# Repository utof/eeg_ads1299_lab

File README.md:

# ADS1299 Learning Lab

**Start without buying anything.** This is a runnable Python learning environment for EEG-like signals, an illustrative electrode/input circuit, signed 24-bit conversion, data transport, signal quality, and a small machine-learning experiment.

It is **not a finished EEG recorder, a validated PCB, or permission to attach a circuit to a person**. The firmware is a board-dependent **bench-only starter** using the ADS1299's internal test/short circuits. **Rev A selects an ADS1299-4 daughterboard plus ESP32-S3-DevKitC-1-N8R8 for simulation/schematic work; none of the hardware-review or body-connection gates are approved.**

## Open these first

| File | What it does for you |
|---|---|
| [START_HERE.html](START_HERE.html) | Offline visual walkthrough, provisional digital pin map, interactive gain/offset calculator. Open with the rest of the repository available. |
| [Agent instructions](AGENTS.md) / [GitHub publication runbook](docs/REPOSITORY_PUBLICATION.md) | Fresh assistant starts here; working publication methods, review boundaries and recovery checks. |
| [Development guide](docs/DEVELOPMENT.md) | Locked installation, one quality command, test-first changes, strict typing, and enforced public interfaces. |
| [DX validation record](docs/DX_VALIDATION.md) | A dated CI run with software tests, actual ngspice execution, native helper tests, and limitations. |
| [Historical results report](docs/RESULTS.md) | Original measured outputs and evidence; retained rather than overwritten by routine CI. |
| [Learning guide](docs/LEARNING_GUIDE.md) | A beginner explanation of the electronics, simulations, signal processing, and small exercises. |
| [Hardware guide](docs/HARDWARE_GUIDE.md) | Purchasing gate, $100 budget constraint, conditional wiring, bench tests, and the body-connection boundary. |
| [Rev A hardware baseline](docs/HARDWARE_BASELINE_REV_A.md) | Selected ADS1299-4 + ESP32-S3 components, machine-readable BOM/profile, fail-closed gates, and ordered next work. |
| [Experiments guide](docs/EXPERIMENTS.md) | From synthetic alpha to a future controlled meditation experiment, without confusing artifacts with consciousness. |
| [Next-session handoff](docs/LLM_HANDOFF.md) | Give this to a future assistant together with the source and validation records. |

The earlier uploaded reports are background, not software dependencies. This package does not depend on their old ZIP links or on an AD8232/ADS1115.

**For assistant-run repository work:** follow the [hosted capability preflight](docs/REPOSITORY_PUBLICATION.md#hosted-capability-preflight)
before proposing downloads or local setup. The installation commands below are
for people choosing to run the lab locally, not prerequisites for hosted editing
or KiCad validation through the connected tools.

## First run: Linux, macOS, or Windows

Use Python **3.11 or newer**; Python 3.13 is the development default. CI exercises clean locked installations on Linux with Python 3.11 and 3.13. macOS and Windows are not currently covered by that CI matrix. `pyproject.toml` and `uv.lock` define the current dependencies; `requirements-tested.txt` is a historical validation record.

Clone or extract the repository, then open a terminal **inside `eeg_ads1299_lab`**:

```bash
uv sync --locked --all-extras
uv run --locked python run_lab.py demo
uv run --locked python -m tools.check
```

Install **uv 0.12.18** first using the [official installation instructions](https://docs.astral.sh/uv/getting-started/installation/). The standalone installer supports an explicit version in its URL. All project commands use `uv`; do not use a separately activated environment or bare Python/pip to run or modify this project. The editable installation makes imports work outside the checkout too.

The demo makes `reports/demo/synthetic_recording.npz`, event/quality CSVs, an analysis JSON, and four PNG figures. Live commands default to ignored `reports/`; committed `results/` examples are historical evidence. Use `--out reports/my_demo` for a separate run. The seed is fixed, but numerical outputs can vary slightly across dependency versions.

The quality command checks formatting, Ruff lint, strict Pyrefly typing, cognitive complexity, Tach import boundaries, the hardware baseline, software tests, and measured branch coverage. It includes the hardware-baseline tests that formerly needed a separate discovery command. Logs and reports go under `reports/check/`, not over historical evidence.

**A successful software check is not a native-simulator, firmware-target, or hardware pass.** Run the explicit native command below for native integration. `uv run --locked python run_lab.py verify` is now a compatibility entry point to the **same** `tools.check` gate. Add `--native` for native integration; `--require-ngspice` remains an alias. There is no competing historical-report verifier.

Before making changes, read [AGENTS.md](AGENTS.md) and install both the pre-commit and commit-message hooks:

```bash
uv run --locked pre-commit install
```

## Run a circuit simulation

```bash
uv run --locked python run_lab.py circuits --out reports/circuits
```

This solves the existing illustrative passive circuit using Python's linear algebra, writes response/tolerance CSVs, and exports two `.cir` files. The numerical solver is **not ngspice**. There is no transistor-level ADS1299 model, and the next Rev A-specific input-network model is separate work.

For a real ngspice cross-check and the full native gate on Debian/Ubuntu/Linux Mint:

```bash
sudo apt update
sudo apt install --no-install-recommends ngspice g++ nodejs
uv run --locked python run_lab.py circuits --require-ngspice --out reports/circuits
uv run --locked python -m tools.check --native
```

The strict commands fail when required tools are absent. The DX CI run recorded in [DX_VALIDATION.md](docs/DX_VALIDATION.md) actually executed ngspice and compared both educational circuits with the independent numerical solution. That newer CI evidence does not change what ran in the original historical validation environment. Simulator logs remain under the output folder.

## Three useful changes

```bash
# Negative control: remove the planted condition difference.
uv run --locked python run_lab.py demo --null-effect --out reports/my_null

# Eight physical channels and 60-Hz residual line interference.
uv run --locked python run_lab.py demo --channels 8 --line-hz 60 --out reports/eight_channels

# Edit a copy of this JSON to change gain, offset, or artifact size.
uv run --locked python run_lab.py demo --config configs/demo.json --out reports/custom
```

Changing a JSON changes the **simulation**, not a physical board. The firmware does not read `configs/demo.json` or the board-review worksheet.

## Test the recording path with no electronics

```bash
uv run --locked python -m tools.check --native
```

The native gate includes the real localhost UDP loopback: nine seconds of synthetic packets with samples 1000 and 2000 deliberately omitted, CSV decoding, and a gap-safe quality report. It checks 2,248 accepted packets and two missing samples. Unexpected extra loss causes a failure rather than a reassuring-looking plot. To run only the loopback, use `uv run --locked python -m tools.run_loopback --out reports/loopback`.

For manual control, use two terminals:

```bash
# Terminal A
uv run --locked python run_lab.py receive --seconds 15 --out reports/practice.bin
```

```bash
# Terminal B, while A is listening
uv run --locked python run_lab.py replay --seconds 8 --drop-every 1000
```

Then:

```bash
uv run --locked python run_lab.py decode reports/practice.bin --out reports/practice.csv
uv run --locked python run_lab.py inspect reports/practice.csv --out reports/practice_quality
```

Keep the `.json` metadata beside the decoded CSV. New captures include a SHA-256 binding the pair; inspection rejects a mismatched generation. Legacy captures without a digest remain readable with an explicit caution. The inspector analyzes only uninterrupted four-second windows. It reports DC offset separately and never fills gaps to manufacture a continuous spectrum. The receiver defaults to localhost; actual LAN use requires `--host 0.0.0.0`, private-network firewall permission, and the computer's LAN address in the firmware. UDP is unencrypted; never expose the port to the public internet.

## What is in the source?

```text
lab/adc.py              Ideal code scaling, range/headroom checks, sinc³ model
lab/analog/            Public analog facade; internal solver, SPICE, and report modules
lab/data_types.py      Typed numerical arrays and data/report contracts
lab/validation.py      Runtime validation at external-data boundaries
lab/signals.py          Deterministic, explicitly synthetic recordings
lab/dsp.py              Quality screens, band power, session-held-out classifier
lab/protocol.py         ADS frame decoding, custom packets, CRC and counters
lab/acquisition.py      UDP/optional bench serial logging and CSV decoding
lab/inspect_capture.py  Gap-safe bench spectra and quality reports
lab/recording.py        Synthetic recording validation and atomic NPZ persistence
lab/pipeline.py         Demo outputs and figures; compatibility persistence re-exports
hardware/rev_a/         Hardware-contract facade, checker, data, and tests
firmware/              Original-ESP32 bench starter; NOT target-compiled by the DX gate
configs/               Editable demo settings and hardware-review worksheet
results/               Historical example recordings, figures, logs, and reports
reports/               Ignored outputs from current quality/simulation runs
tests/                 Regression, property, architecture, and workflow tests
tools/check.py         Shared local/CI quality command
tools/commit_messages.py Conventional Commit hook and actual-history validation
tach.toml              Enforced public interfaces and dependency direction
```

The firmware's default `BOARD_PROFILE_REVIEWED = false` intentionally prevents acquisition startup. Changing that setting acknowledges **bench digital wiring only**, not body-use approval. Do not bypass it just to see a waveform.

## Rev A input-network study

The selected Rev A input components now feed a reproducible passive-network study, rather than remaining isolated hardware JSON. Start with the numerical calculation; then run the independent simulator comparison when ngspice is installed:

```bash
uv run --locked python -m lab.rev_a --out reports/rev_a_input
uv run --locked python -m lab.rev_a --require-ngspice --out reports/rev_a_input_native
```

The study validates and loads the locked 4.99 kOhm / 4.7 nF component values and BOM tolerances, checks an ideal-source reference, compares balanced and mismatched source impedances, evaluates eight tolerance corners per case, and reports 50/60 Hz common-mode conversion plus hypothetical DC leakage sensitivity. The native command actually runs six ngspice comparisons. `uv run --locked python -m tools.check --native` includes this study and retains its evidence under `reports/check/rev_a_input/`.

All source/load/parasitic assumptions appear in the report. Clamps remain DNP. **This is not an ADS1299 silicon, distributed-cable, BIAS-loop, physical-hardware or human-use safety model.** Read the [Rev A study guide](docs/REV_A_INPUT_STUDY.md) before interpreting the numbers.

## Contributing: uv and Conventional Commits

Use `uv sync --locked --all-extras` and `uv run --locked ...` for project work. Child processes launched with `sys.executable` inherit that locked interpreter; they do not create a second environment. CI bootstraps uv itself separately, then uses the same locked commands.

Commit subjects follow [Conventional Commits 1.0.0](https://www.conventionalcommits.org/en/v1.0.0/):

```text
feat(simulation): add a Rev A input-network sweep
fix(recording): reject discontinuous sample times
refactor(acquisition): stream decoded packets
chore(dx): synchronize issue labels
```

Use lowercase `feat`, `fix`, `docs`, `style`, `refactor`, `perf`, `test`, `build`, `ci`, `chore`, or `revert`; an optional lowercase scope describes the affected component. A breaking change uses `!` after the type/scope and should explain the incompatibility in a `BREAKING CHANGE:` footer. Subjects must have a nonempty description and no trailing whitespace.

The installed `commit-msg` hook checks the subject. CI checks **actual commits introduced by the PR**, not just its title. Old history is grandfathered. Actual merge commits are exempt, but writing “Merge” on a single-parent commit is not a bypass. **Merge PRs with merge commits: no squash and no history rewriting.** Validate a range locally with:

```bash
uv run --locked python -m tools.commit_messages --base origin/main --head HEAD
uv run --locked python -m tools.check --native
```

Issues use one `type/*`, one `priority/*`, and applicable `area/*` labels. Examples: `type/bug` + `priority/high` + `area/acquisition`, or `type/refactor` + `priority/medium` + `area/dx`. [The label manifest](.github/labels.json) owns names, colors, and descriptions; trusted-main housekeeping synchronizes it without deleting unrelated labels. Merged same-repository PR branches are removed only after ancestry and exact-head checks. Active or changed branches are retained.

Read [the adversarial review](docs/ADVERSARIAL_REVIEW.md) for the architecture verdict, reproduced failures, corrections, and remaining limits.

## Troubleshooting

| Symptom | First action |
|---|---|
| `ModuleNotFoundError` | Run `uv sync --locked --all-extras` and use `uv run --locked` with the repository environment. |
| Missing ngspice or native compiler | Install the required tool; do not count numerical Python tests as native execution. |
| Quality gate failed | Read the named log and `reports/check/CHECK_REPORT.json`; do not bypass the check. |
| `All epochs rejected` | Inspect gain, differential DC offset, and quality flags. An overrange input is an expected negative test. |
| No UDP packets | First repeat localhost loopback. Then inspect the private LAN address, firewall, and UDP port. |
| No four-second spectral windows | The capture is too short or fragmented. Fix acquisition before interpreting spectra. |
| Unexpected ESP32 or board pins | Stop; the supplied firmware pin map is not generic to every ESP32/ADS1299 module. |
| Matplotlib cache permission warning | Set `MPLCONFIGDIR` to a writable directory; no special font installation is required. |

Read [SOURCES.md](docs/SOURCES.md) for primary references and [MODEL_SCOPE.md](docs/MODEL_SCOPE.md) for model boundaries.

### Bounded BIAS overload hypothesis

`uv run --locked python -m lab.rev_a_bias_overload --require-ngspice` compares
a stated one-pole rail/slew hypothesis with ngspice while preserving feedback
capacitor charge. It is not measured ADS1299 overload recovery. Read
[the scope, source limits and numerical checks](docs/REV_A_BIAS_OVERLOAD.md).

### Shared-source analog-feed hypothesis

Run `uv run --locked python -m lab.rev_a_supply` for five independently checked
startup/burst cases of the selected analog-feed path. See
[the study and its assumptions](docs/REV_A_SUPPLY_STUDY.md). A completed numerical
comparison may expose a modeled rail-margin breach; neither outcome qualifies
the board or the separate TPS7A20 model.

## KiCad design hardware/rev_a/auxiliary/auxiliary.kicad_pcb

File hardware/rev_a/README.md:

# Rev A component baseline

Read [the hardware decision](../../docs/HARDWARE_BASELINE_REV_A.md) first.

**Selected:** ADS1299-4PAGR, ESP32-S3-DevKitC-1-N8R8, internal ADC reference/clock,
5 V unipolar bench power, and ADC-only TPS7A2033PDBVR regulation.

**Not authorized:** fabrication, purchasing, external-input operation or body connection.
The review flags are deliberately false. These JSON files are a design contract,
not a firmware implementation or a validated KiCad schematic.

```bash
python hardware/rev_a/check_baseline.py
python -m unittest discover -s hardware/rev_a -p 'test_*.py' -v
```

Run those commands from the repository root. Python 3.10+ and no third-party
packages are required. The checker also works when invoked by absolute path.

- `board_profile.json`: selected operating point, proposed GPIO/header assignments and review gates.
- `bom.json`: exact selected MPNs, reference counts, FIT/DNP population and planning costs.
- `sources.json`: primary sources, original-report SHA-256 hashes and access limitations.

This baseline was integrated after inspecting live `main` at
`31205de841c577c373532fbc9d065fa81d0a6ac8`. The existing firmware remains
unchanged and its board/target review guard stays fail-closed. The repository's
entry-point docs link here so future work does not reopen the component decision
by accident. Run the existing project tests and ngspice baseline on this branch
before changing the analog model or porting firmware to the S3.

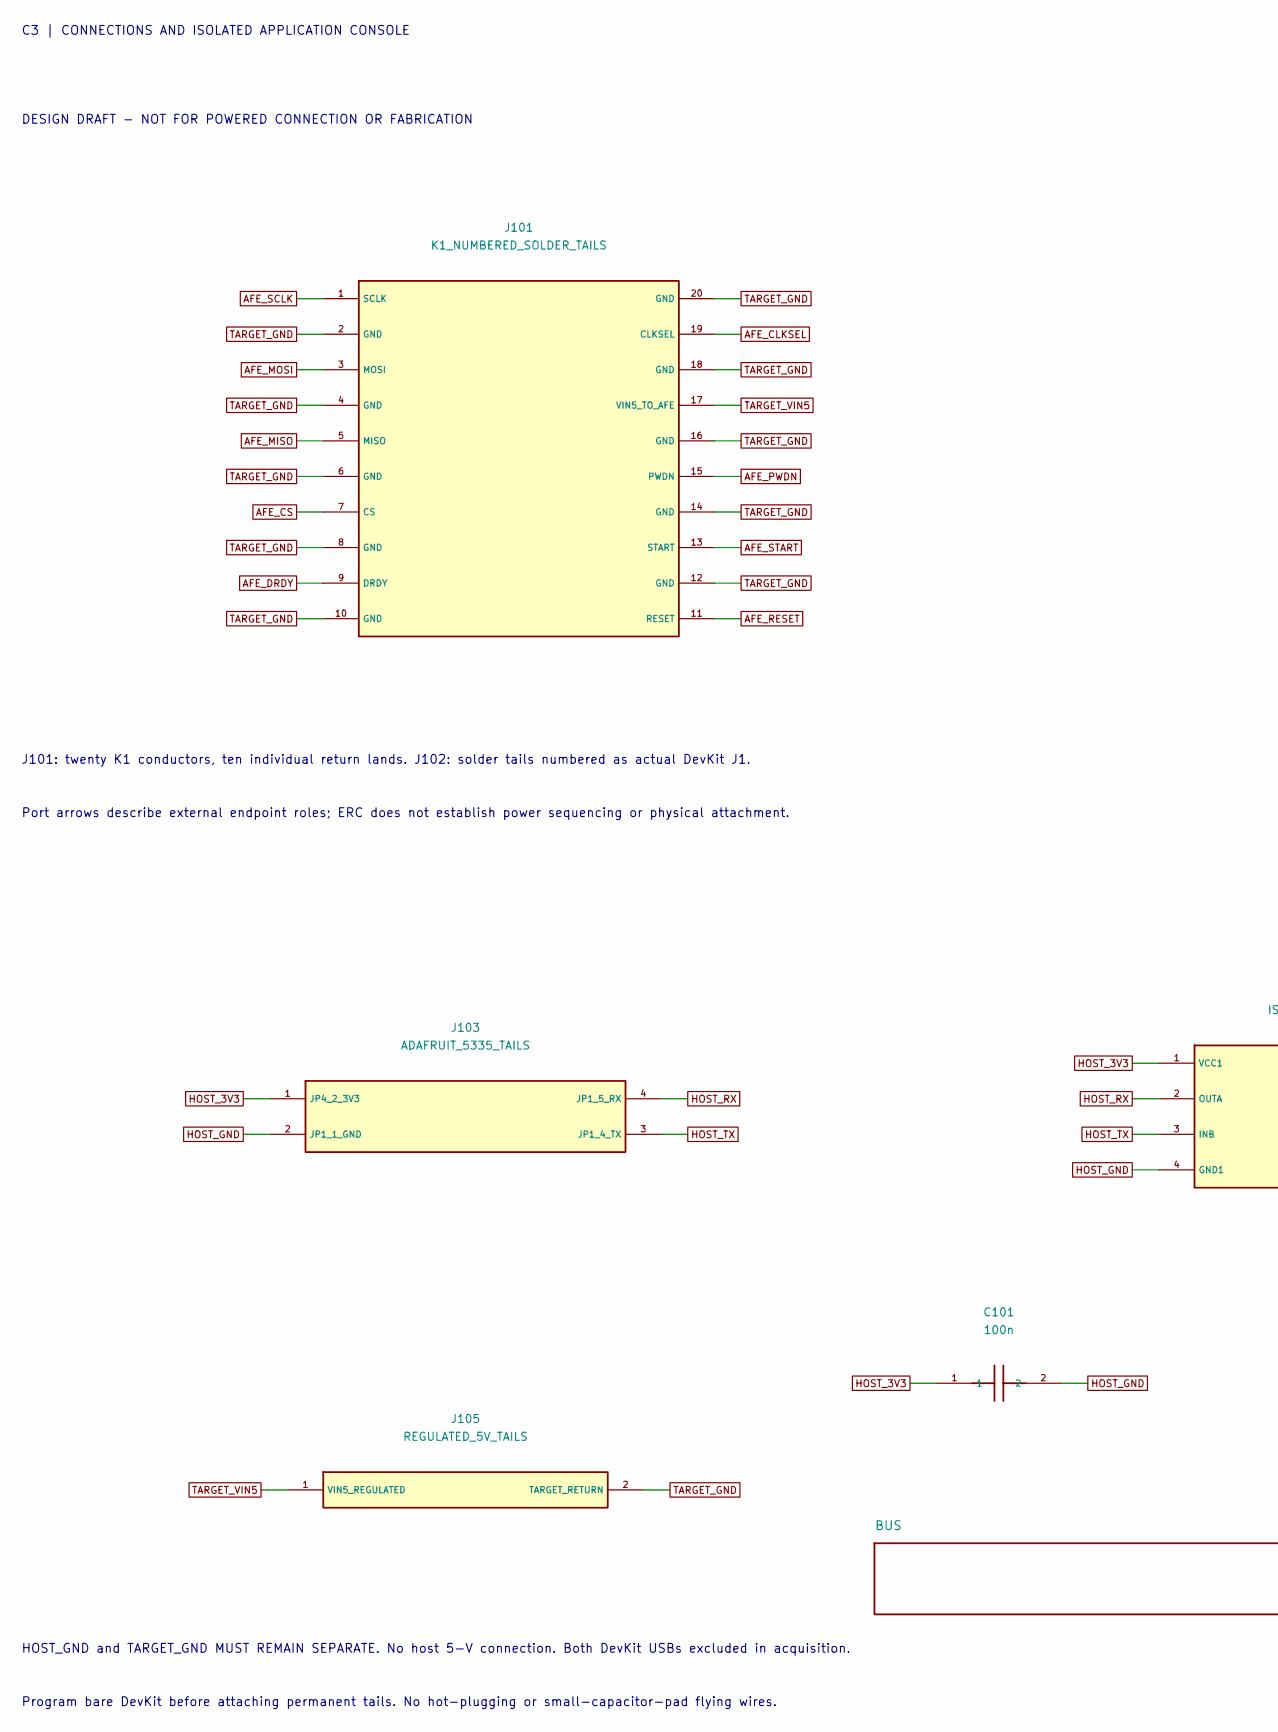
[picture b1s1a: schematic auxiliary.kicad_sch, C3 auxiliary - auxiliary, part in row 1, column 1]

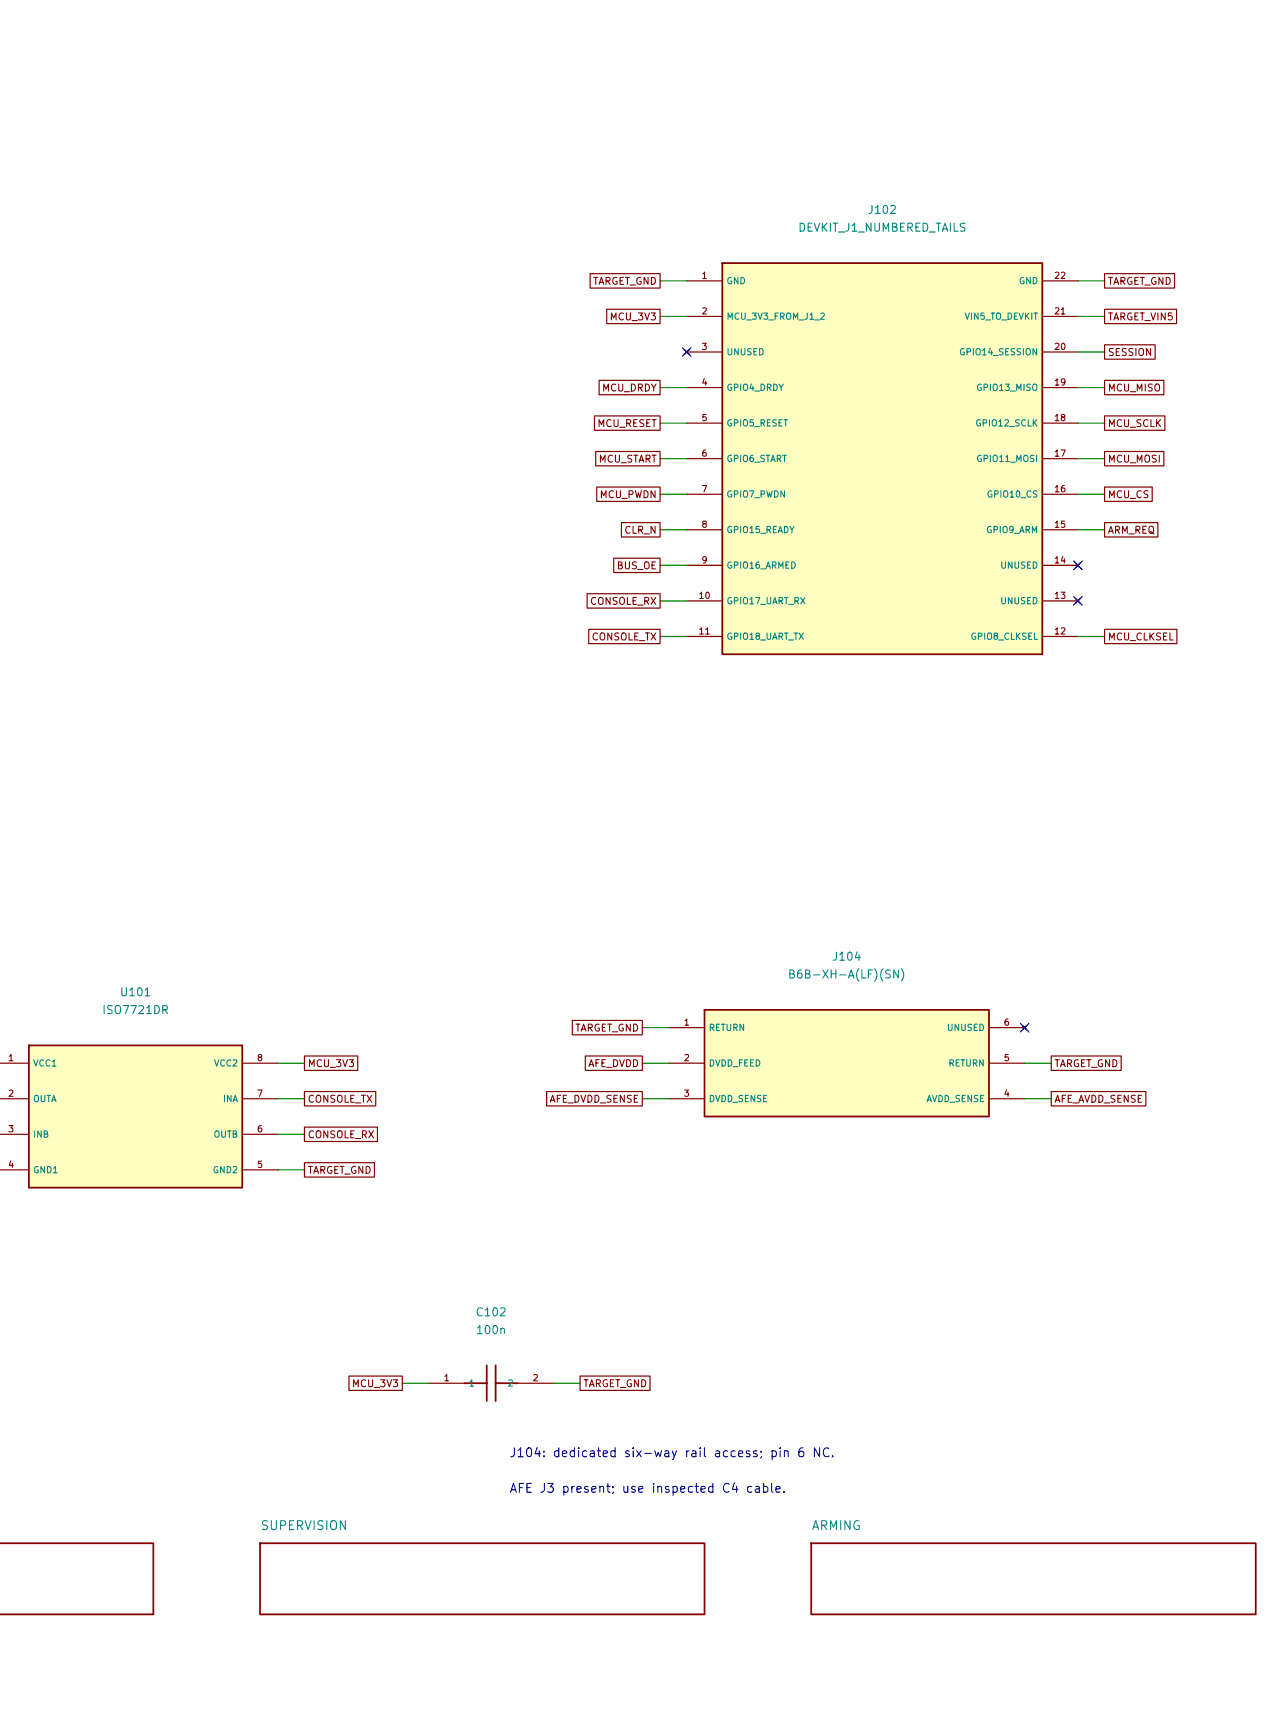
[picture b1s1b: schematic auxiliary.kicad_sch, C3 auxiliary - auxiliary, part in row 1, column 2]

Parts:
C101, C102: 100n; C_0603_1608Metric; MPN C0603C104K5RACTU
J101: K1_NUMBERED_SOLDER_TAILS; SolderTails_20; MPN PCB_LANDINGS_ONLY
J102: DEVKIT_J1_NUMBERED_TAILS; SolderTails_22; MPN PCB_LANDINGS_ONLY
J103: ADAFRUIT_5335_TAILS; SolderTails_4; MPN PCB_LANDINGS_ONLY
J104: B6B-XH-A(LF)(SN); JST_XH_B6B-XH-A_1x06_P2.50mm_Vertical; MPN B6B-XH-A(LF)(SN)
J105: REGULATED_5V_TAILS; SolderTails_2; MPN PCB_LANDINGS_ONLY
U101: ISO7721DR; SOIC-8_3.9x4.9mm_P1.27mm; MPN ISO7721DR

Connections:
AFE_AVDD_SENSE: J104.4 (AVDD_SENSE); also elsewhere on the board
AFE_CLKSEL: J101.19 (CLKSEL); also elsewhere on the board
AFE_CS: J101.7 (CS); also elsewhere on the board
AFE_DRDY: J101.9 (DRDY); also elsewhere on the board
AFE_DVDD: J104.2 (DVDD_FEED); also elsewhere on the board
AFE_DVDD_SENSE: J104.3 (DVDD_SENSE); also elsewhere on the board
AFE_MISO: J101.5 (MISO); also elsewhere on the board
AFE_MOSI: J101.3 (MOSI); also elsewhere on the board
AFE_PWDN: J101.15 (PWDN); also elsewhere on the board
AFE_RESET: J101.11 (RESET); also elsewhere on the board
AFE_SCLK: J101.1 (SCLK); also elsewhere on the board
AFE_START: J101.13 (START); also elsewhere on the board
ARM_REQ: J102.15 (GPIO9_ARM); also elsewhere on the board
BUS_OE: J102.9 (GPIO16_ARMED); also elsewhere on the board
CLR_N: J102.8 (GPIO15_READY); also elsewhere on the board
CONSOLE_RX: J102.10 (GPIO17_UART_RX), U101.6 (OUTB)
CONSOLE_TX: J102.11 (GPIO18_UART_TX), U101.7 (INA)
HOST_3V3: C101.1, J103.1 (JP4_2_3V3), U101.1 (VCC1)
HOST_GND: C101.2, J103.2 (JP1_1_GND), U101.4 (GND1)
HOST_RX: J103.4 (JP1_5_RX), U101.2 (OUTA)
HOST_TX: J103.3 (JP1_4_TX), U101.3 (INB)
MCU_3V3: C102.1, J102.2 (MCU_3V3_FROM_J1_2), U101.8 (VCC2); also elsewhere on the board
MCU_CLKSEL: J102.12 (GPIO8_CLKSEL); also elsewhere on the board
MCU_CS: J102.16 (GPIO10_CS); also elsewhere on the board
MCU_DRDY: J102.4 (GPIO4_DRDY); also elsewhere on the board
MCU_MISO: J102.19 (GPIO13_MISO); also elsewhere on the board
MCU_MOSI: J102.17 (GPIO11_MOSI); also elsewhere on the board
MCU_PWDN: J102.7 (GPIO7_PWDN); also elsewhere on the board
MCU_RESET: J102.5 (GPIO5_RESET); also elsewhere on the board
MCU_SCLK: J102.18 (GPIO12_SCLK); also elsewhere on the board
MCU_START: J102.6 (GPIO6_START); also elsewhere on the board
SESSION: J102.20 (GPIO14_SESSION); also elsewhere on the board
TARGET_GND: C102.2, J101.2 (GND), J101.4 (GND), J101.6 (GND), J101.8 (GND), J101.10 (GND), J101.12 (GND), J101.14 (GND), J101.16 (GND), J101.18 (GND), J101.20 (GND), J102.1 (GND), J102.22 (GND), J104.1 (RETURN), J104.5 (RETURN), J105.2 (TARGET_RETURN), U101.5 (GND2); also elsewhere on the board
TARGET_VIN5: J101.17 (VIN5_TO_AFE), J102.21 (VIN5_TO_DEVKIT), J105.1 (VIN5_REGULATED); also elsewhere on the board

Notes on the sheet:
C3 | CONNECTIONS AND ISOLATED APPLICATION CONSOLE
DESIGN DRAFT - NOT FOR POWERED CONNECTION OR FABRICATION
J101: twenty K1 conductors, ten individual return lands. J102: solder tails numbered as actual DevKit J1.
Port arrows describe external endpoint roles; ERC does not establish power sequencing or physical attachment.
J104: dedicated six-way rail access; pin 6 NC.
AFE J3 present; use inspected C4 cable.
HOST_GND and TARGET_GND MUST REMAIN SEPARATE. No host 5-V connection. Both DevKit USBs excluded in acquisition.
Program bare DevKit before attaching permanent tails. No hot-plugging or small-capacitor-pad flying wires.

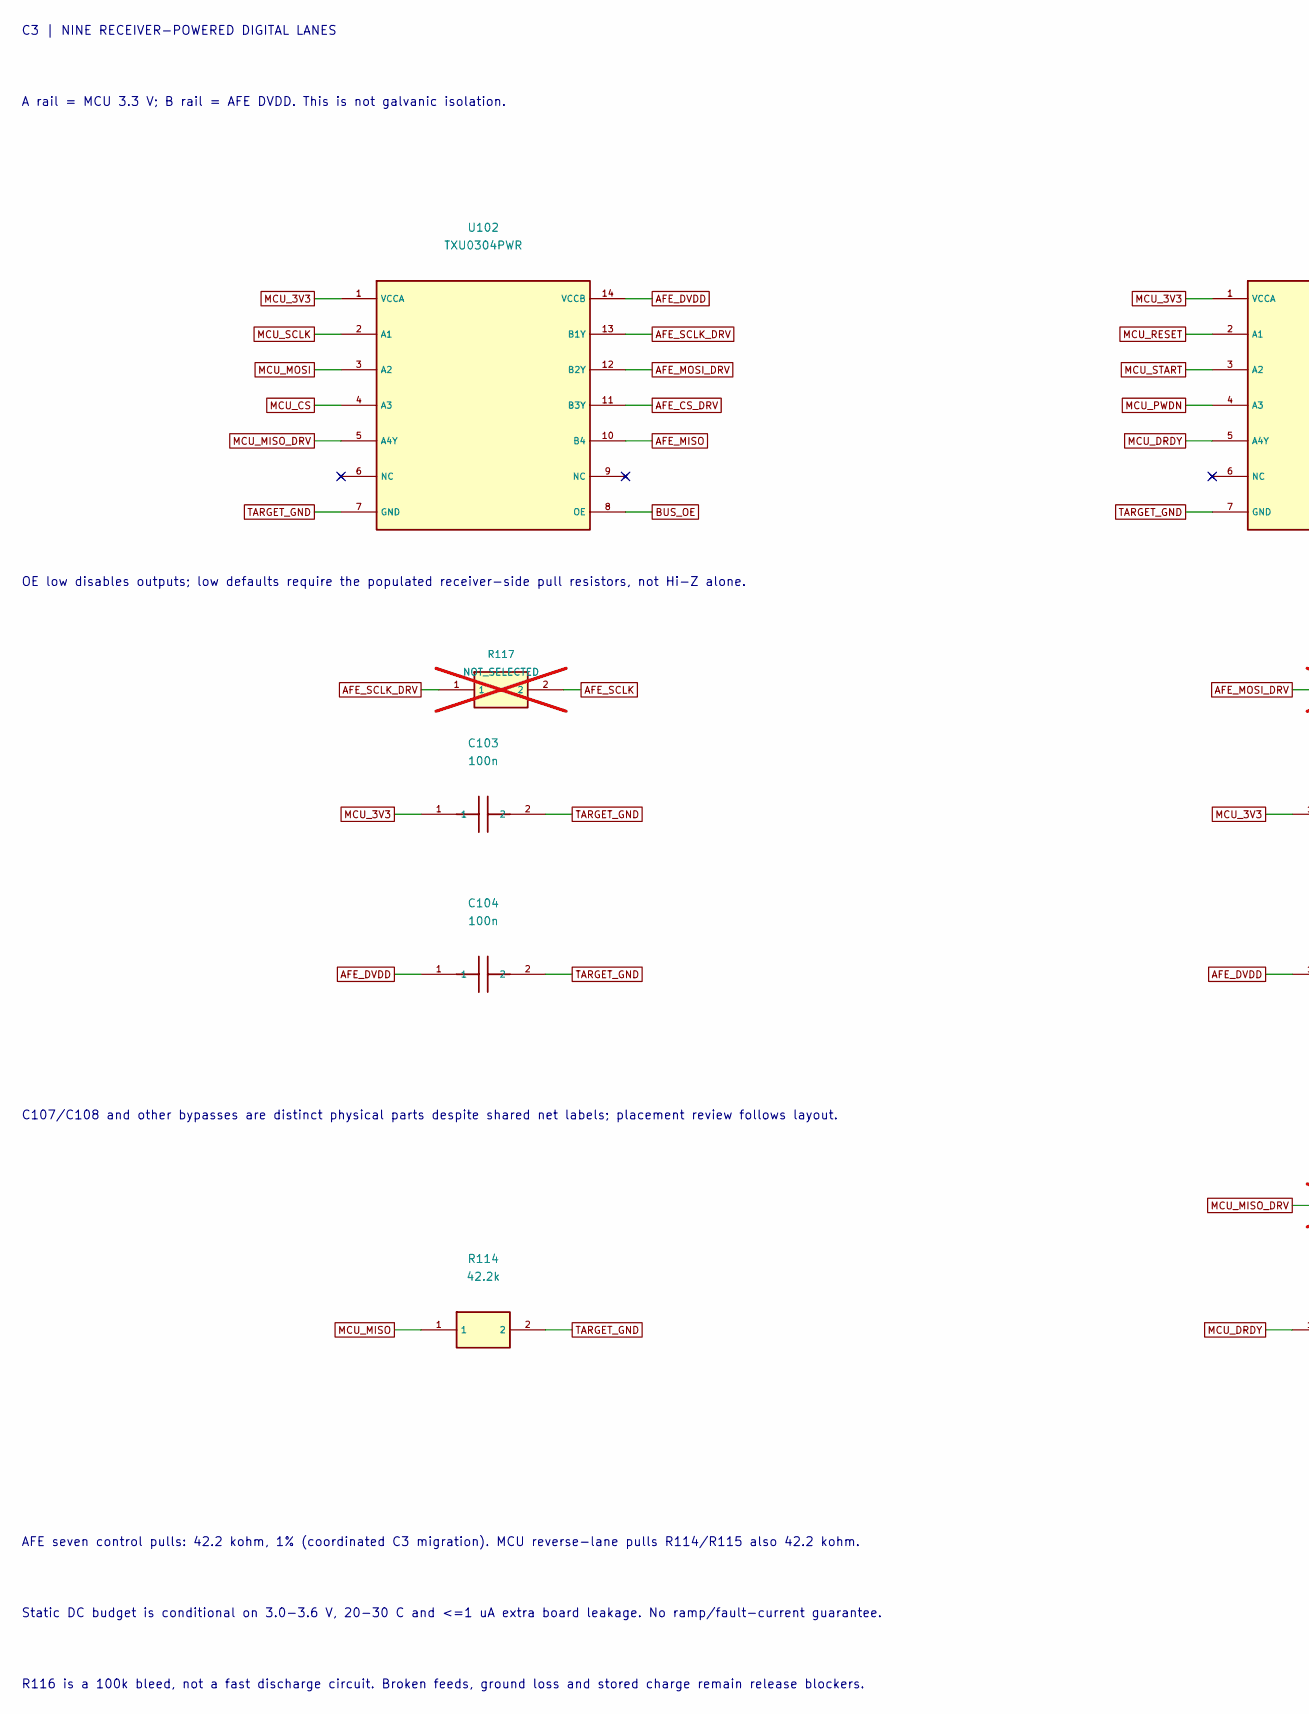
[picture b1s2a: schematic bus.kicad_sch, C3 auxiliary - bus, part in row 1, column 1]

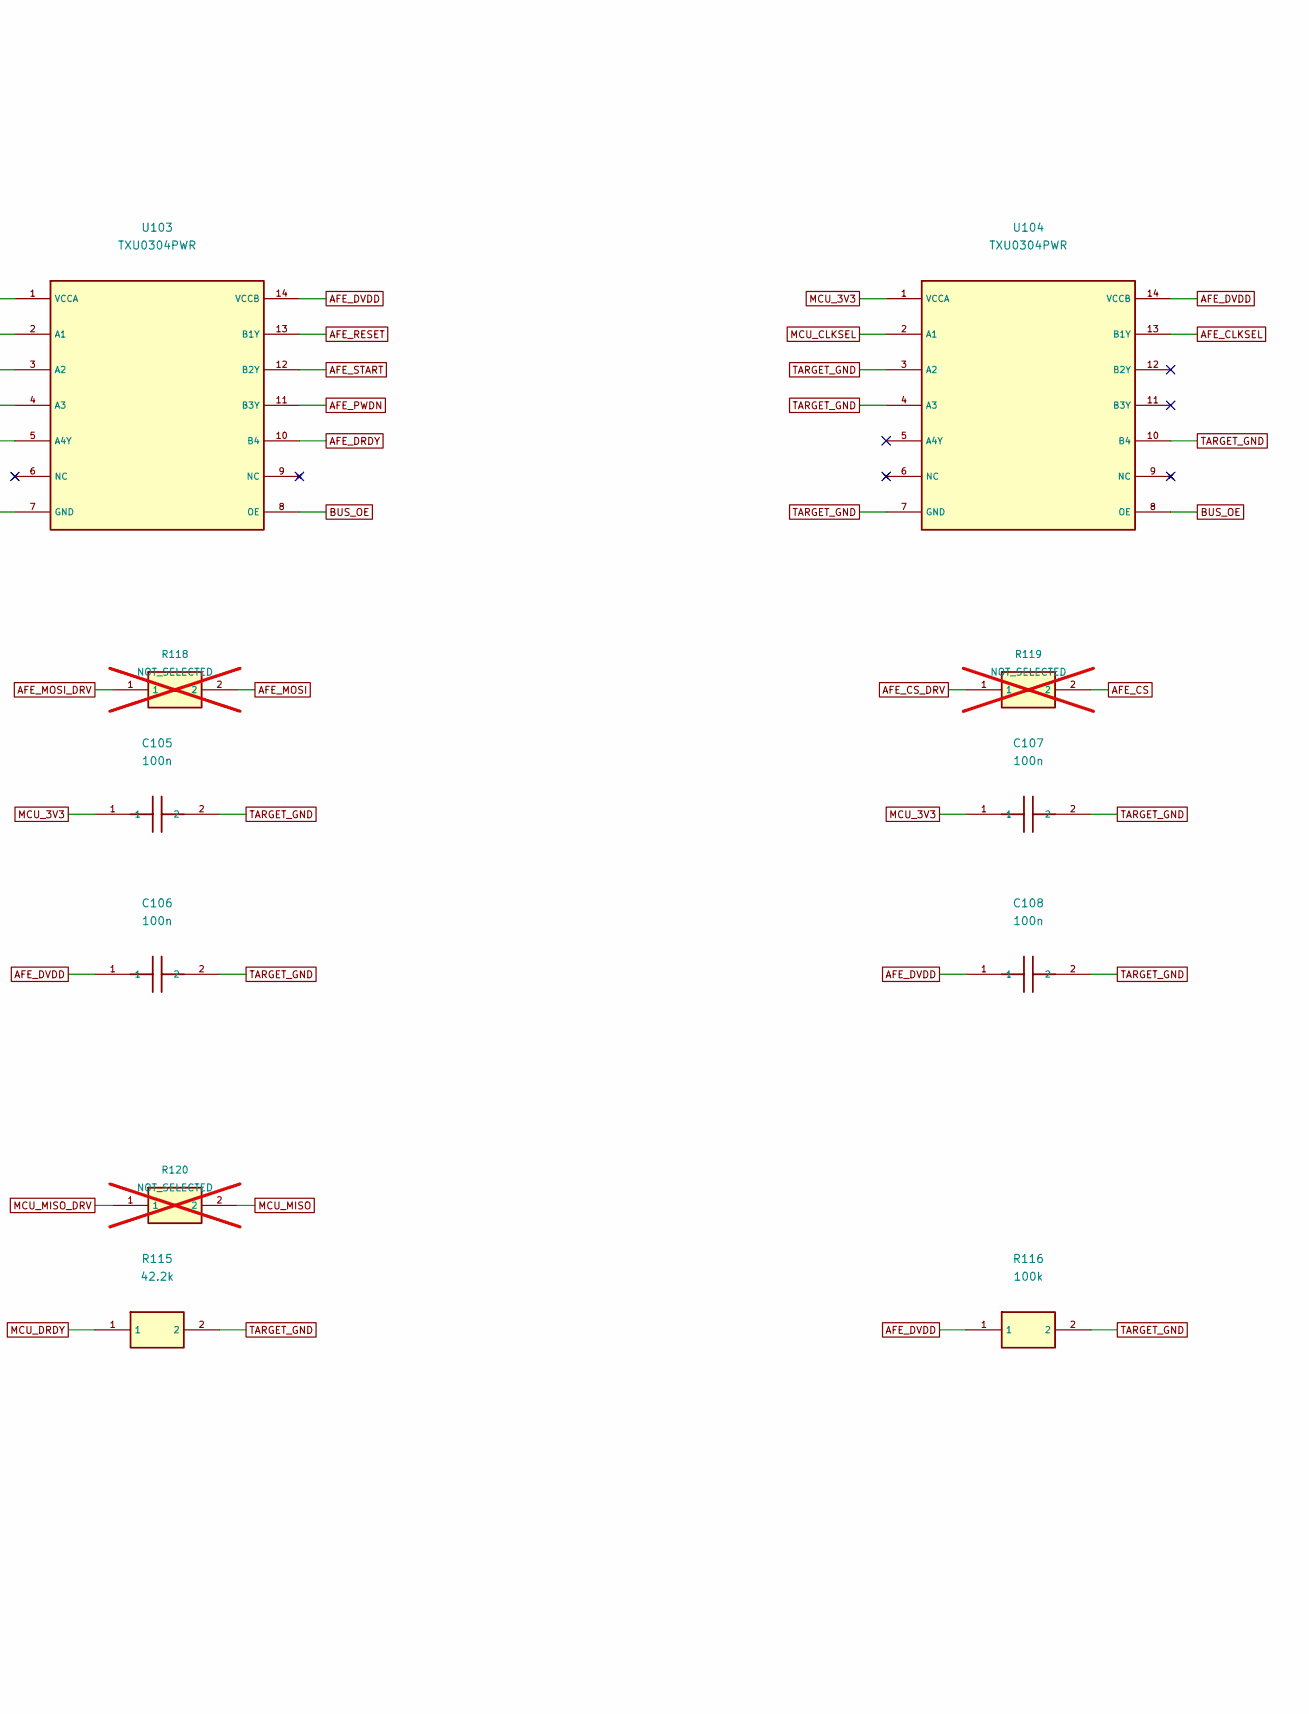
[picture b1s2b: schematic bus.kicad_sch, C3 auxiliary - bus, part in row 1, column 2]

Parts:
C103, C104, C105, C106, C107, C108: 100n; C_0603_1608Metric; MPN C0603C104K5RACTU
R114, R115: 42.2k; R_0603_1608Metric; MPN RC0603FR-0742K2L
R116: 100k; R_0603_1608Metric; MPN RC0603FR-07100KL
R117, R118, R119, R120: NOT_SELECTED; R_0603_1608Metric; MPN NOT_SELECTED; not fitted
U102, U103, U104: TXU0304PWR; TSSOP-14_4.4x5mm_P0.65mm; MPN TXU0304PWR

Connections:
AFE_CLKSEL: U104.13 (B1Y); also elsewhere on the board
AFE_CS: R119.2; also elsewhere on the board
AFE_CS_DRV: R119.1, U102.11 (B3Y)
AFE_DRDY: U103.10 (B4); also elsewhere on the board
AFE_DVDD: C104.1, C106.1, C108.1, R116.1, U102.14 (VCCB), U103.14 (VCCB), U104.14 (VCCB); also elsewhere on the board
AFE_MISO: U102.10 (B4); also elsewhere on the board
AFE_MOSI: R118.2; also elsewhere on the board
AFE_MOSI_DRV: R118.1, U102.12 (B2Y)
AFE_PWDN: U103.11 (B3Y); also elsewhere on the board
AFE_RESET: U103.13 (B1Y); also elsewhere on the board
AFE_SCLK: R117.2; also elsewhere on the board
AFE_SCLK_DRV: R117.1, U102.13 (B1Y)
AFE_START: U103.12 (B2Y); also elsewhere on the board
BUS_OE: U102.8 (OE), U103.8 (OE), U104.8 (OE); also elsewhere on the board
MCU_3V3: C103.1, C105.1, C107.1, U102.1 (VCCA), U103.1 (VCCA), U104.1 (VCCA); also elsewhere on the board
MCU_CLKSEL: U104.2 (A1); also elsewhere on the board
MCU_CS: U102.4 (A3); also elsewhere on the board
MCU_DRDY: R115.1, U103.5 (A4Y); also elsewhere on the board
MCU_MISO: R114.1, R120.2; also elsewhere on the board
MCU_MISO_DRV: R120.1, U102.5 (A4Y)
MCU_MOSI: U102.3 (A2); also elsewhere on the board
MCU_PWDN: U103.4 (A3); also elsewhere on the board
MCU_RESET: U103.2 (A1); also elsewhere on the board
MCU_SCLK: U102.2 (A1); also elsewhere on the board
MCU_START: U103.3 (A2); also elsewhere on the board
TARGET_GND: C103.2, C104.2, C105.2, C106.2, C107.2, C108.2, R114.2, R115.2, R116.2, U102.7 (GND), U103.7 (GND), U104.3 (A2), U104.4 (A3), U104.7 (GND), U104.10 (B4); also elsewhere on the board

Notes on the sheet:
C3 | NINE RECEIVER-POWERED DIGITAL LANES
A rail = MCU 3.3 V; B rail = AFE DVDD. This is not galvanic isolation.
OE low disables outputs; low defaults require the populated receiver-side pull resistors, not Hi-Z alone.
C107/C108 and other bypasses are distinct physical parts despite shared net labels; placement review follows layout.
AFE seven control pulls: 42.2 kohm, 1% (coordinated C3 migration). MCU reverse-lane pulls R114/R115 also 42.2 kohm.
Static DC budget is conditional on 3.0-3.6 V, 20-30 C and <=1 uA extra board leakage. No ramp/fault-current guarantee.
R116 is a 100k bleed, not a fast discharge circuit. Broken feeds, ground loss and stored charge remain release blockers.

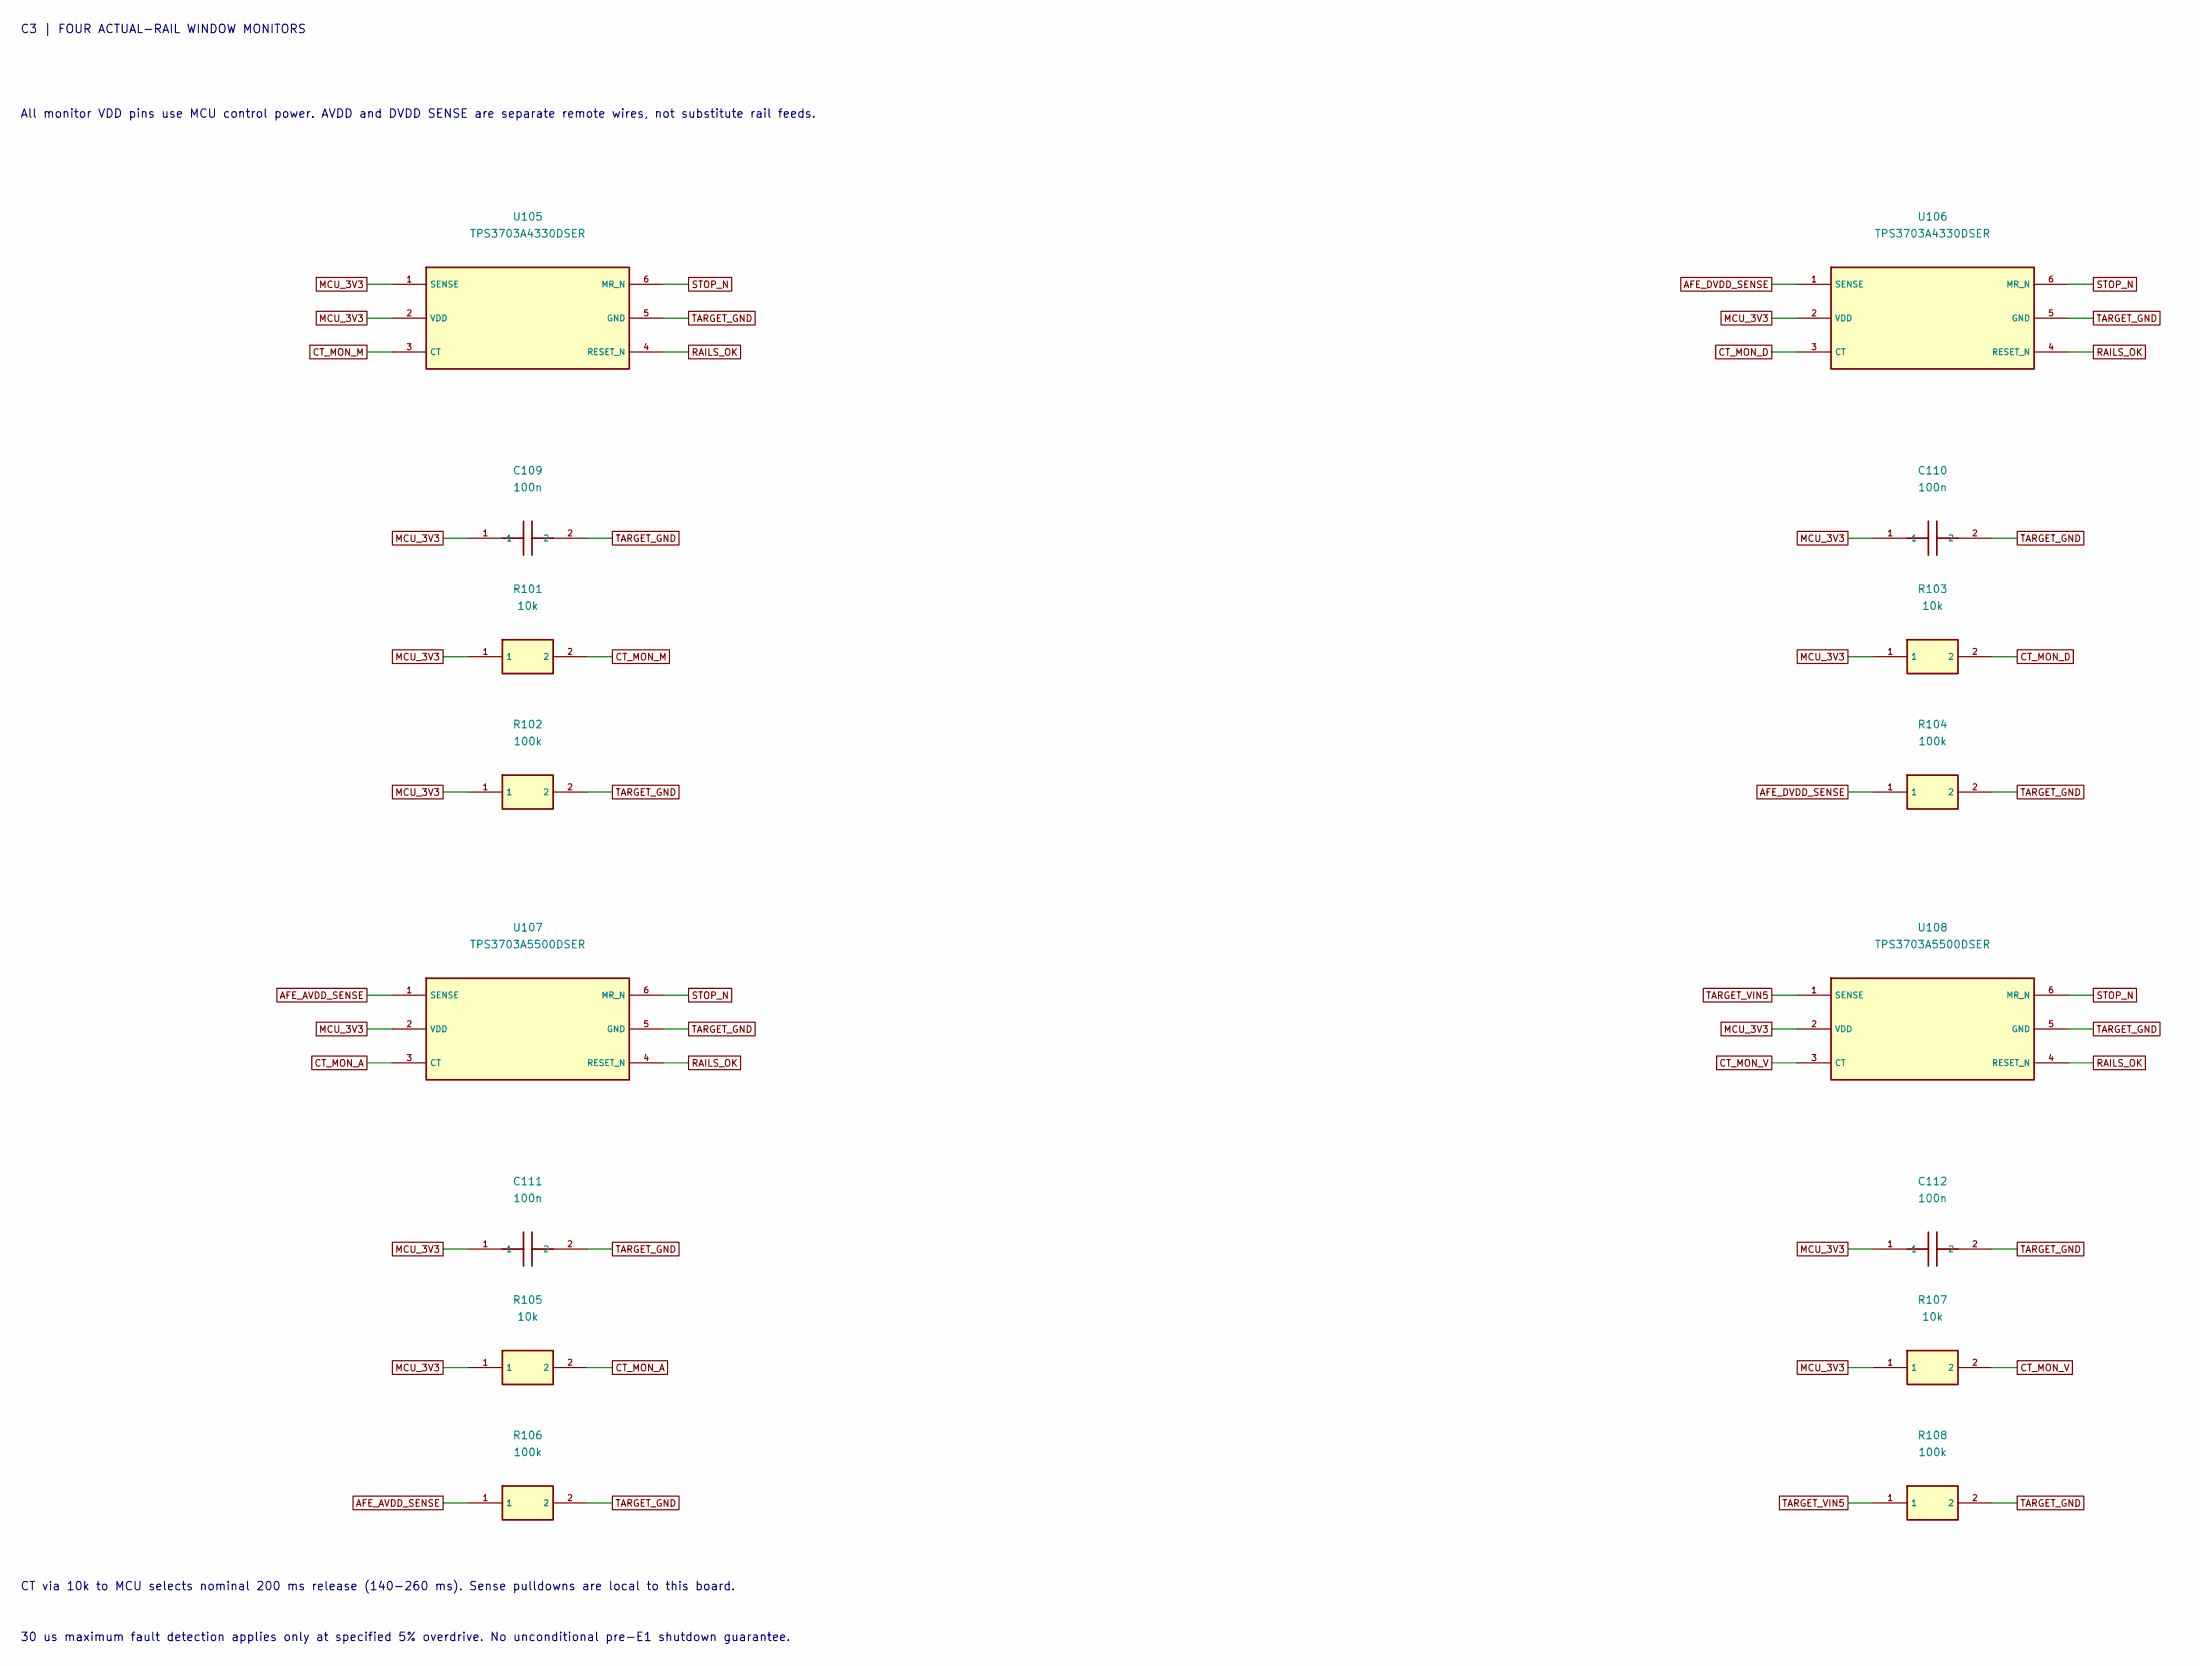
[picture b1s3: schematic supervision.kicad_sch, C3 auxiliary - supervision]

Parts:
C109, C110, C111, C112: 100n; C_0603_1608Metric; MPN C0603C104K5RACTU
R101, R103, R105, R107: 10k; R_0603_1608Metric; MPN RC0603FR-0710KL
R102, R104, R106, R108: 100k; R_0603_1608Metric; MPN RC0603FR-07100KL
U105, U106: TPS3703A4330DSER; WSON-6_1.5x1.5mm_P0.5mm; MPN TPS3703A4330DSER
U107, U108: TPS3703A5500DSER; WSON-6_1.5x1.5mm_P0.5mm; MPN TPS3703A5500DSER

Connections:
AFE_AVDD_SENSE: R106.1, U107.1 (SENSE); also elsewhere on the board
AFE_DVDD_SENSE: R104.1, U106.1 (SENSE); also elsewhere on the board
CT_MON_A: R105.2, U107.3 (CT)
CT_MON_D: R103.2, U106.3 (CT)
CT_MON_M: R101.2, U105.3 (CT)
CT_MON_V: R107.2, U108.3 (CT)
MCU_3V3: C109.1, C110.1, C111.1, C112.1, R101.1, R102.1, R103.1, R105.1, R107.1, U105.1 (SENSE), U105.2 (VDD), U106.2 (VDD), U107.2 (VDD), U108.2 (VDD); also elsewhere on the board
RAILS_OK: U105.4 (RESET_N), U106.4 (RESET_N), U107.4 (RESET_N), U108.4 (RESET_N); also elsewhere on the board
STOP_N: U105.6 (MR_N), U106.6 (MR_N), U107.6 (MR_N), U108.6 (MR_N); also elsewhere on the board
TARGET_GND: C109.2, C110.2, C111.2, C112.2, R102.2, R104.2, R106.2, R108.2, U105.5 (GND), U106.5 (GND), U107.5 (GND), U108.5 (GND); also elsewhere on the board
TARGET_VIN5: R108.1, U108.1 (SENSE); also elsewhere on the board

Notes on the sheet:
C3 | FOUR ACTUAL-RAIL WINDOW MONITORS
All monitor VDD pins use MCU control power. AVDD and DVDD SENSE are separate remote wires, not substitute rail feeds.
CT via 10k to MCU selects nominal 200 ms release (140-260 ms). Sense pulldowns are local to this board.
30 us maximum fault detection applies only at specified 5% overdrive. No unconditional pre-E1 shutdown guarantee.
